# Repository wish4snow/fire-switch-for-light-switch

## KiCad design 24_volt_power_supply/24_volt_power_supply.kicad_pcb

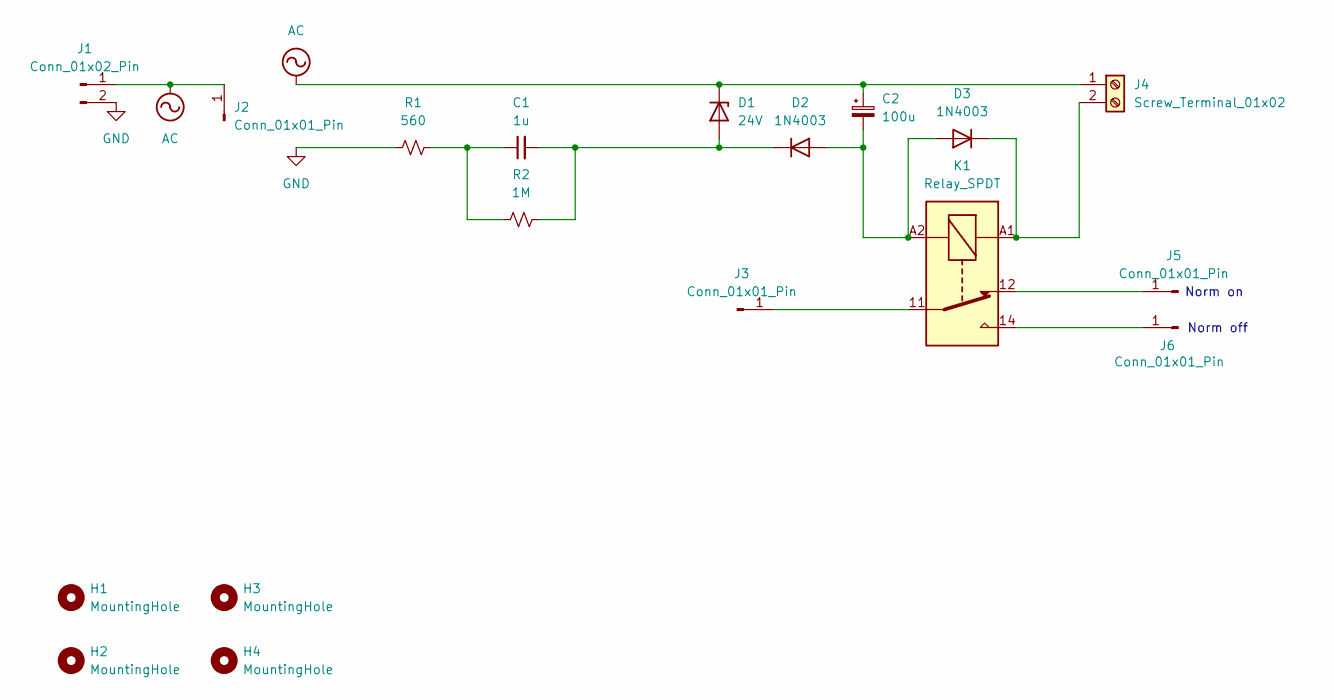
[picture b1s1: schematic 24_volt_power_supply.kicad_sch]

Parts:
C1: 1u; C_Rect_L26.5mm_W11.5mm_P22.50mm_MKS4
C2: 100u; CP_Radial_D5.0mm_P2.00mm
D1: 24V; D_A-405_P7.62mm_Horizontal
D2, D3: 1N4003; D_DO-41_SOD81_P10.16mm_Horizontal
H1, H2, H3, H4: MountingHole; MountingHole_3.2mm_M3_ISO14580_Pad_TopOnly
J1: Conn_01x02_Pin; SolderWire-2.5sqmm_1x02_P7.2mm_D2.4mm_OD3.6mm
J2, J3, J5, J6: Conn_01x01_Pin; SolderWire-2.5sqmm_1x01_D2.4mm_OD3.6mm
J4: Screw_Terminal_01x02; TerminalBlock_MetzConnect_Type011_RT05502HBLC_1x02_P5.00mm_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
K1: Relay_SPDT; Relay_Cit_J1071CS24VDC.36
R1: 560; R_Axial_DIN0516_L15.5mm_D5.0mm_P20.32mm_Horizontal
R2: 1M; R_Axial_DIN0207_L6.3mm_D2.5mm_P7.62mm_Horizontal

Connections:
AC: C2.1, D1.1 (K), J1.1, J2.1, J4.1
GND: J1.2, R1.1
unnamed: C1.1, R1.2, R2.1
unnamed: C1.2, D1.2 (A), D2.1 (K), R2.2
unnamed: C2.2, D2.2 (A), D3.2 (A), K1.A2
unnamed: D3.1 (K), J4.2, K1.A1
unnamed: J3.1, K1.11
unnamed: J5.1, K1.12
unnamed: J6.1, K1.14

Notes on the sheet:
Norm off
Norm on

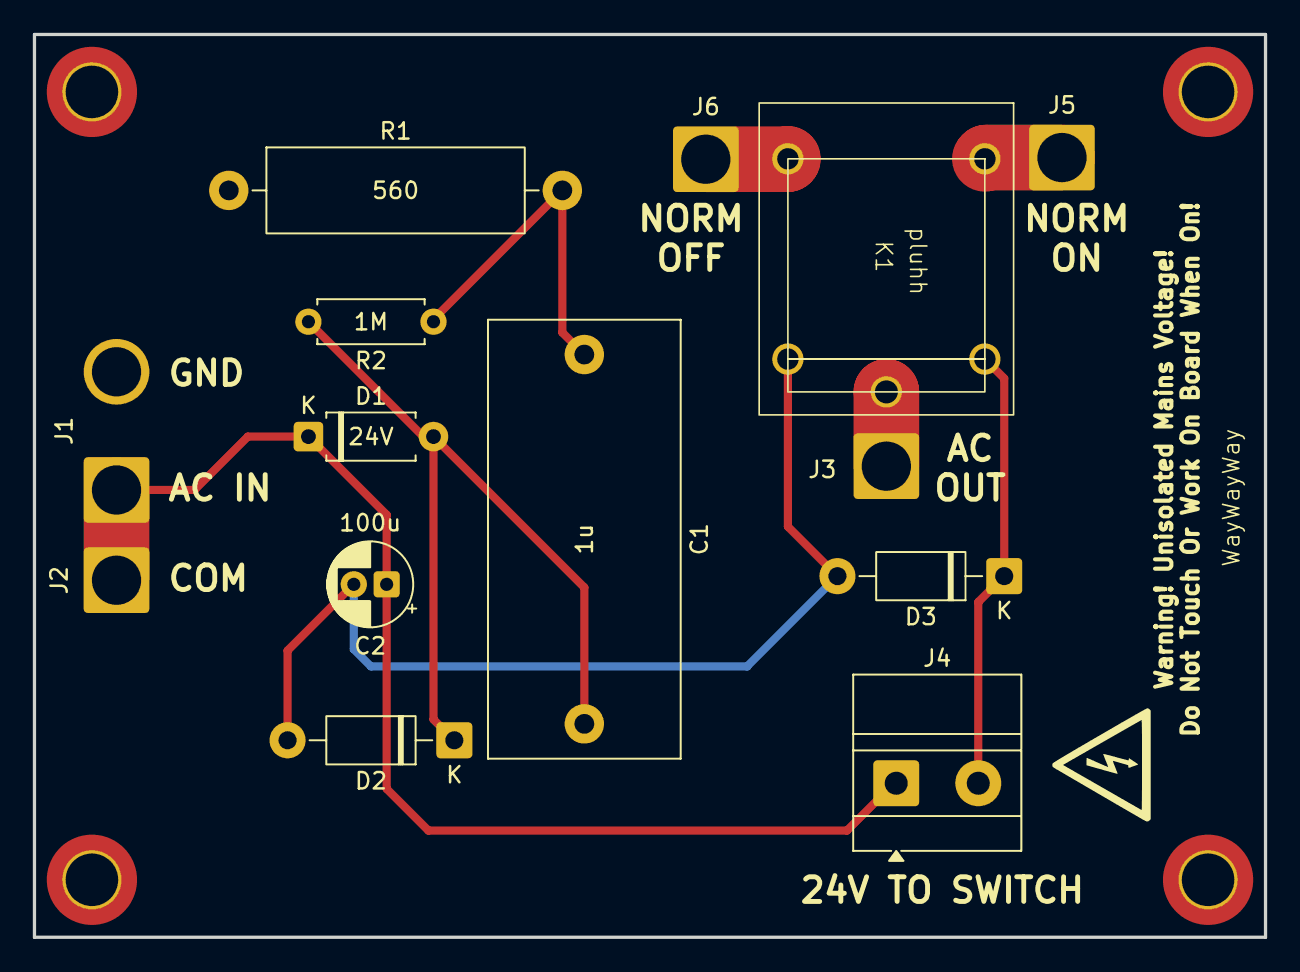
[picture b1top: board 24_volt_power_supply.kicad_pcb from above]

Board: 2 copper layers, 75.0 x 55.0 mm, 18 parts (0 on the bottom side), 9 nets.

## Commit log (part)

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2026-06-05 fixed D2 location
2026-06-11 added footprints to wire and screw connections
2026-06-11 added .gitignore
2026-06-11 added footprint to 1M resisor
2026-06-11 added footprint to 100uf cap
2026-06-11 lk did too much to write :/
2026-06-12 started making pcb
2026-06-12 finished first iteration of pcb
2026-06-12 need to fix odd pcb routings
2026-06-12 increased trace thickness for high power
2026-06-12 fixed gnd plane issues
2026-06-13 added freewheeling diode
2026-06-14 new directory for 3d models
2026-06-14 made mounting feature to alarm
2026-06-14 added sidewall
2026-06-14 fixed mounting hole locations
2026-06-14 fixed freewheeling diode direction
2026-06-14 updated pcb
2026-06-14 fixed case holes
2026-06-14 fixed mounting hole location
2026-06-15 made 2 hole solution for mo~unting case
2026-06-22 started using spreadsheats for sizing
2026-06-22 remade model to work better with spreadsheet
2026-06-22 used original values for spreadsheet
2026-06-22 added pocket
2026-06-22 added mounting features
2026-06-22 added fillets to reduce stress on part
2026-06-22 got rid of visible sketches
2026-06-22 started wall mount for case
2026-06-23 added mounting features to wall mount
2026-06-23 added mounting holes for case
2026-06-23 made assembly
2026-06-26 added cutout and mounting holes for junction box
2026-06-26 started mounting holes for pcb
2026-06-26 made net spacing to clear mounting hole even for all corners
2026-06-26 fixed spacing for trace and mounting hole. NEED TO FIX LIVE WIRE TRACES, TOO THIN
2026-06-30 added mounting features to case_wall_mount. NEED TO FIX LIVE WIRE TRACES, TOO THIN
